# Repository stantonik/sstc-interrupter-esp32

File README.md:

# sstc-interrupter-esp32

**Still in development! Maybe unstable.**

> This project implements a digital interrupter for any Solid State Tesla Coils (SSTC, DRSSTC, ...). The interrupter allows precise control over the arc output using different control modes, making it easy to experiment with pulse timing or MIDI control.

## Features
- **Three Control Modes**
    - Manual: Fully custom PWM output from 0 to 20 kHz, with 1 µs minimum pulse width.
    - USB MIDI: Supports up to 8 simultaneous notes

- **User Interface**
    - SSD1306 64x128 monochrome display
    - Rotary encoder for navigation
    - Two triggers: toggle switch and push button
    - Nice and simple graphical interface

- **Connectivity**
    - USB-C OTG/Serial for MIDI/Programming
    - Toslink SPDIF output

- **Hardware Efficiency**
    - Written entirely in C using ESP-IDF
    - Real-time control via FreeRTOS
    - Optimized for ESP32-S3 hardware
    - Battery powered (200 mAh)

## Demonstration

Playing *Kavinsky - Nighcall*...

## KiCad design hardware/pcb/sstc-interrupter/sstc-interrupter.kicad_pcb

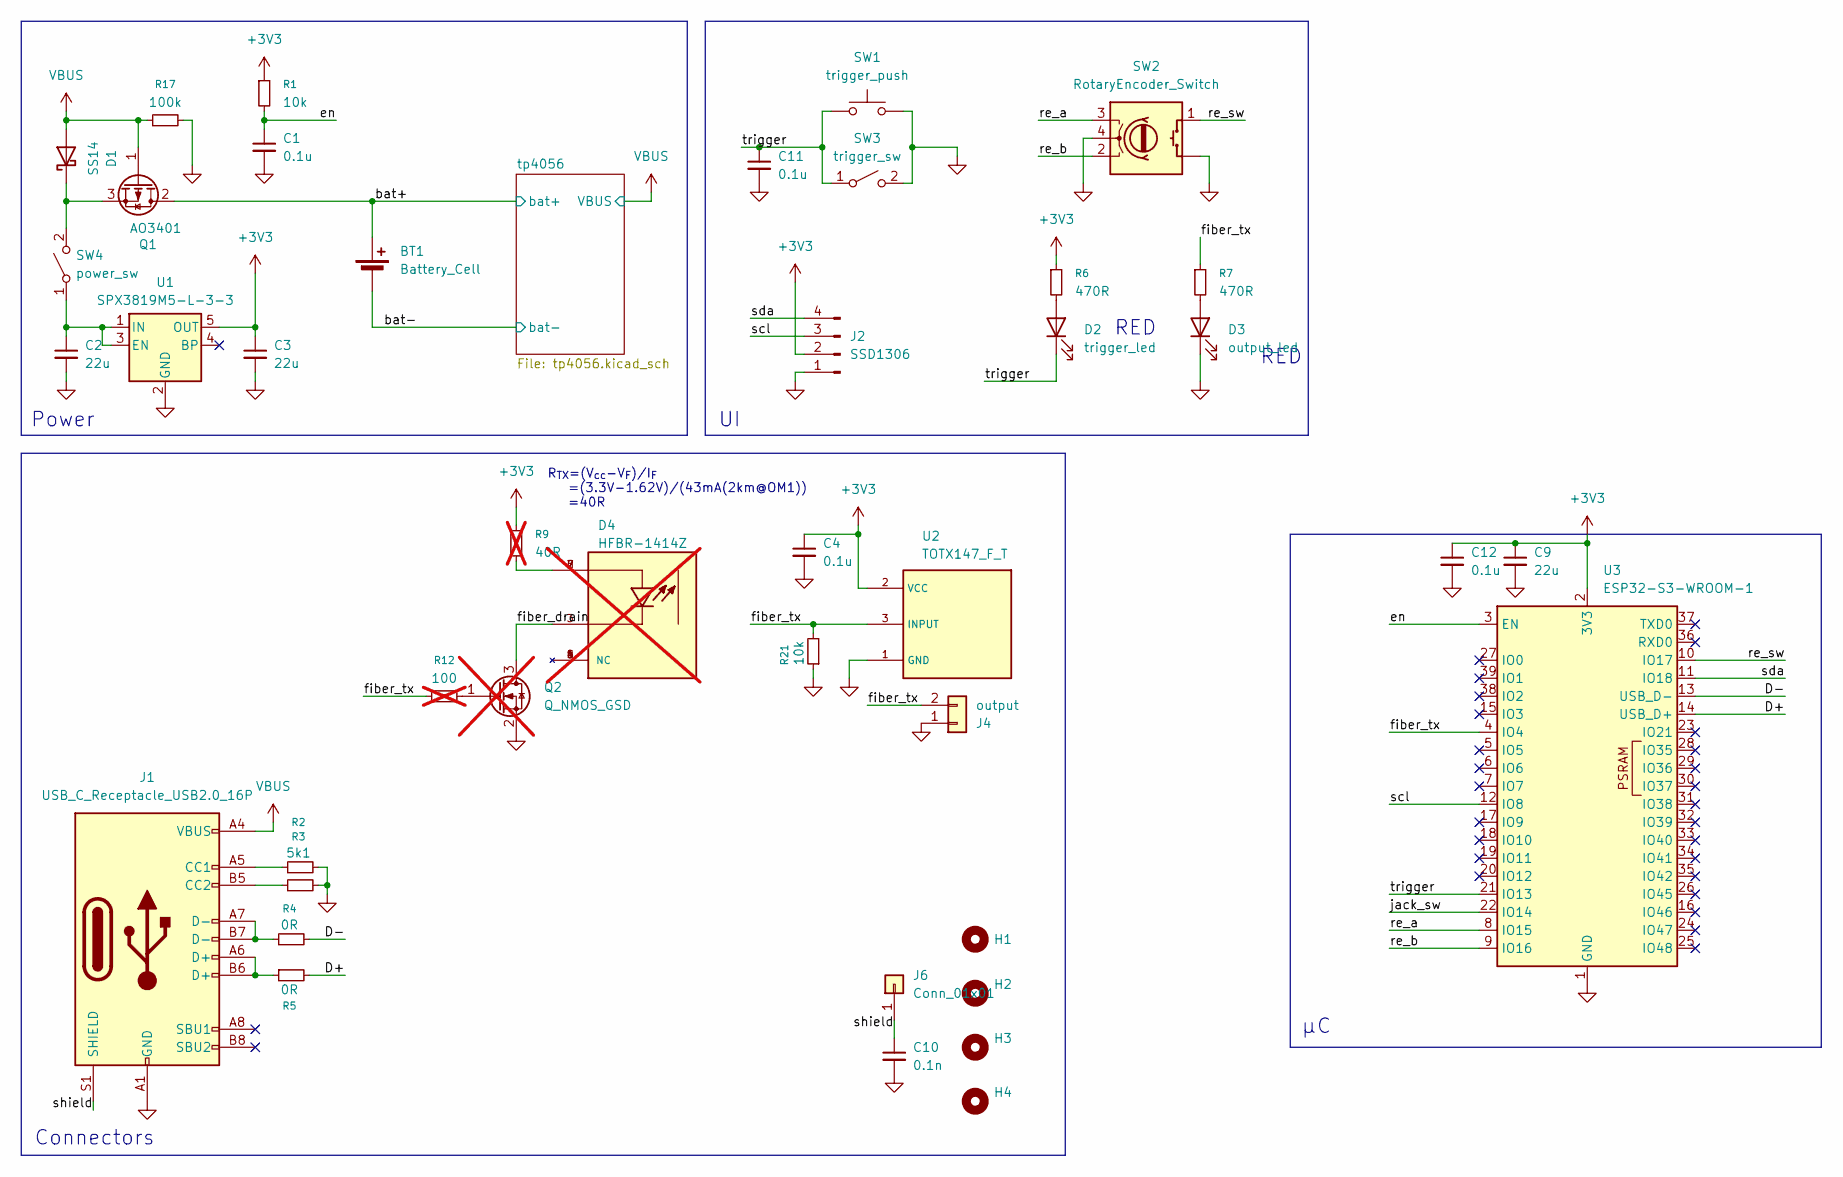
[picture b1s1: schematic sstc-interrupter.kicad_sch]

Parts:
BT1: Battery_Cell; JST_PH_B2B-PH-K_1x02_P2.00mm_Vertical
C1, C4, C11, C12: 0.1u; C_0603_1608Metric_Pad1.08x0.95mm_HandSolder
C2, C3, C9: 22u; C_0805_2012Metric_Pad1.18x1.45mm_HandSolder
C10: 0.1n; C_0805_2012Metric_Pad1.18x1.45mm_HandSolder
D1: SS14; D_SMA
D2: trigger_led; JST_PH_B2B-PH-K_1x02_P2.00mm_Vertical
D3: output_led; JST_PH_B2B-PH-K_1x02_P2.00mm_Vertical
D4: HFBR-1414Z; OPTO_HFBR-1414Z; PARTREV February 15, 2019; not fitted
H1, H2, H3, H4: MountingHole; MountingHole_3.2mm_M3_DIN965
J1: USB_C_Receptacle_USB2.0_16P; USB_C_Receptacle_GCT_USB4105-xx-A_16P_TopMnt_Horizontal
J2: SSD1306; JST_PH_B4B-PH-K_1x04_P2.00mm_Vertical
J4: output; PinHeader_1x02_P2.54mm_Horizontal
J6: Conn_01x01; SolderWire-0.15sqmm_1x01_D0.5mm_OD1.5mm
Q1: AO3401; SOT-23_Handsoldering
Q2: Q_NMOS_GSD; SOT-23-3; not fitted
R1, R21: 10k; R_0603_1608Metric_Pad0.98x0.95mm_HandSolder
R2, R3: 5k1; R_0603_1608Metric_Pad0.98x0.95mm_HandSolder
R4, R5: 0R; R_0603_1608Metric_Pad0.98x0.95mm_HandSolder
R6, R7: 470R; R_0603_1608Metric_Pad0.98x0.95mm_HandSolder
R9: 40R; R_0603_1608Metric_Pad0.98x0.95mm_HandSolder; not fitted
R12: 100; R_0603_1608Metric_Pad0.98x0.95mm_HandSolder; not fitted
R17: 100k; R_0603_1608Metric_Pad0.98x0.95mm_HandSolder
SW1: trigger_push; JST_PH_B2B-PH-K_1x02_P2.00mm_Vertical
SW2: RotaryEncoder_Switch; JST_PH_B4B-PH-K_1x04_P2.00mm_Vertical
SW3: trigger_sw; JST_PH_B2B-PH-K_1x02_P2.00mm_Vertical
SW4: power_sw; JST_PH_B2B-PH-K_1x02_P2.00mm_Vertical
U1: SPX3819M5-L-3-3; SOT-23-5
U2: TOTX147_F_T; TOSHIBA_TORX147_F_T_
U3: ESP32-S3-WROOM-1; ESP32-S3-WROOM-1U

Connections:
+3V3: C3.1, C4.1, C9.1, C12.1, J2.2, R1.1, R6.1, R9.1, U1.5 (OUT), U2.2 (VCC), U3.2 (3V3)
/D+: R5.2, U3.14 (USB_D+)
/D-: R4.2, U3.13 (USB_D-)
/bat+: BT1.1 (+), Q1.2 (D); also elsewhere on the board
/bat-: BT1.2 (-); also elsewhere on the board
/en: C1.1, R1.2, U3.3 (EN)
/fiber_tx: J4.2, R7.1, R12.1, R21.2, U2.3 (INPUT), U3.4 (IO4)
/jack_sw: U3.22 (IO14)
/re_a: SW2.3 (A), U3.8 (IO15)
/re_b: SW2.2 (B), U3.9 (IO16)
/re_sw: SW2.1 (S1), U3.10 (IO17)
/scl: J2.3, U3.12 (IO8)
/sda: J2.4, U3.11 (IO18)
/shield: C10.1, J1.S1 (SHIELD), J6.1 (Pin_1_1)
/trigger: C11.1, D2.2 (K), SW1.1, SW3.1 (A), U3.21 (IO13)
GND: C1.2, C2.2, C3.2, C4.2, C9.2, C10.2, C11.2, C12.2, D3.1 (K), J1.A1 (GND), J1.A12 (GND), J1.B1 (GND), J1.B12 (GND), J2.1, J4.1, Q2.2 (S), R2.2, R3.2, R17.2, R21.1, SW1.2, SW2. (S2), SW2.4 (C), SW3.2 (B), U1.2 (GND), U2.1 (GND), U3.1 (GND), U3.40 (GND), U3.41 (GND); also elsewhere on the board
unnamed: D1.1 (K), Q1.3 (S), SW4.2 (B)
unnamed: D2.1 (A), R6.2
unnamed: D3.2 (A), R7.2
unnamed: D4.1 (NC), D4.4 (NC), D4.5 (NC), D4.8 (NC)
unnamed: D4.2, D4.6, D4.7, R9.2
unnamed: D4.3, Q2.3 (D)
unnamed: J1.A5 (CC1), R2.1
unnamed: J1.B5 (CC2), R3.1
unnamed: J1.A6 (D+), J1.B6 (D+), R5.1
unnamed: J1.A7 (D-), J1.B7 (D-), R4.1
unnamed: Q2.1 (G), R12.2
unnamed: C2.1, SW4.1 (A), U1.1 (IN), U1.3 (EN)
VBUS: D1.2 (A), J1.A4 (VBUS), J1.A9 (VBUS), J1.B4 (VBUS), J1.B9 (VBUS), Q1.1 (G), R17.1; also elsewhere on the board

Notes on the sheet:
Connectors
R_{TX}=(V_{cc}-V_{F})/I_{F} =(3.3V-1.62V)/(43mA(2km@OM1)) =40R
RED
Power

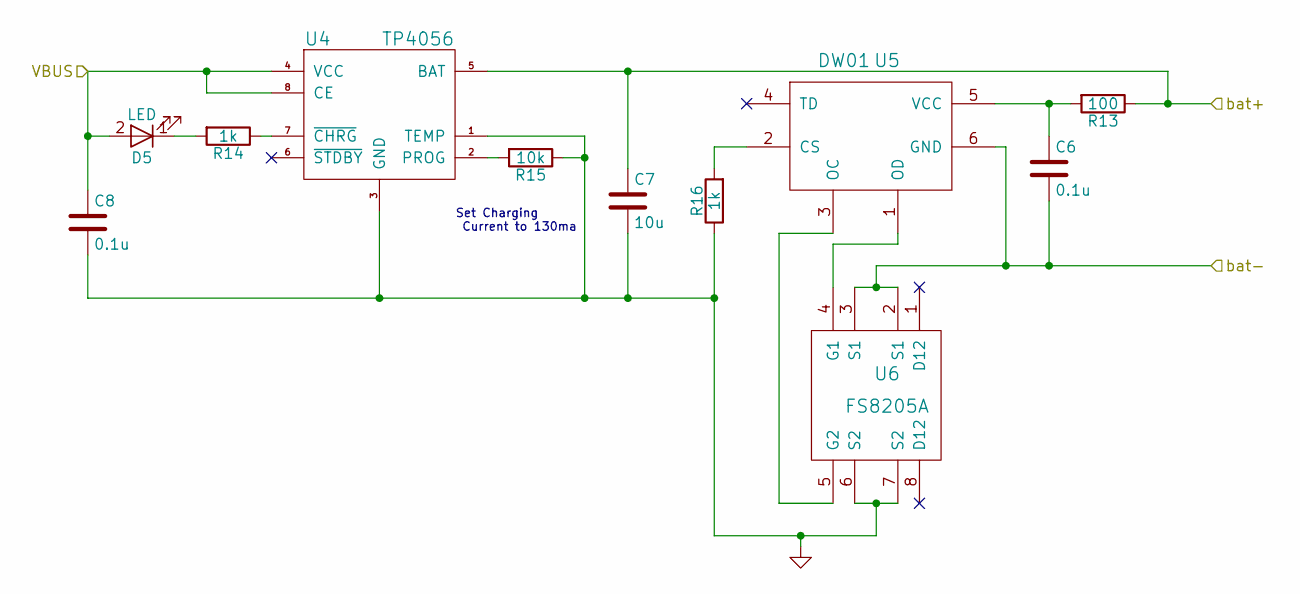
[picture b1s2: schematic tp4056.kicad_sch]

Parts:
C6, C8: 0.1u; C_0603_1608Metric_Pad1.08x0.95mm_HandSolder
C7: 10u; C_0805_2012Metric_Pad1.18x1.45mm_HandSolder
D5: LED; LED_0603_1608Metric_Pad1.05x0.95mm_HandSolder
R13: 100; R_0603_1608Metric_Pad0.98x0.95mm_HandSolder
R14, R16: 1k; R_0603_1608Metric_Pad0.98x0.95mm_HandSolder
R15: 10k; R_0603_1608Metric_Pad0.98x0.95mm_HandSolder
U4: TP4056; SOP-8_3.9x4.9mm_P1.27mm
U5: DW01; SOT-23-6_Handsoldering
U6: FS8205A; TSSOP-8_4.4x3mm_P0.65mm

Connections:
/bat+: C7.1, R13.1, U4.5 (BAT); also elsewhere on the board
/bat-: C6.2, U5.6 (GND), U6.2 (S1), U6.3 (S1); also elsewhere on the board
GND: C7.2, C8.2, R15.1, R16.1, U4.1 (TEMP), U4.3 (GND), U6.6 (S2), U6.7 (S2); also elsewhere on the board
unnamed: D5.1 (K), R14.2
unnamed: R15.2, U4.2 (PROG)
unnamed: R14.1, U4.7 (~CHRG)
unnamed: R16.2, U5.2 (CS)
unnamed: U5.3 (OC), U6.5 (G2)
unnamed: U5.1 (OD), U6.4 (G1)
unnamed: C6.1, R13.2, U5.5 (VCC)
VBUS: C8.1, D5.2 (A), U4.4 (VCC), U4.8 (CE); also elsewhere on the board

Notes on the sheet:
Set Charging Current to 130ma

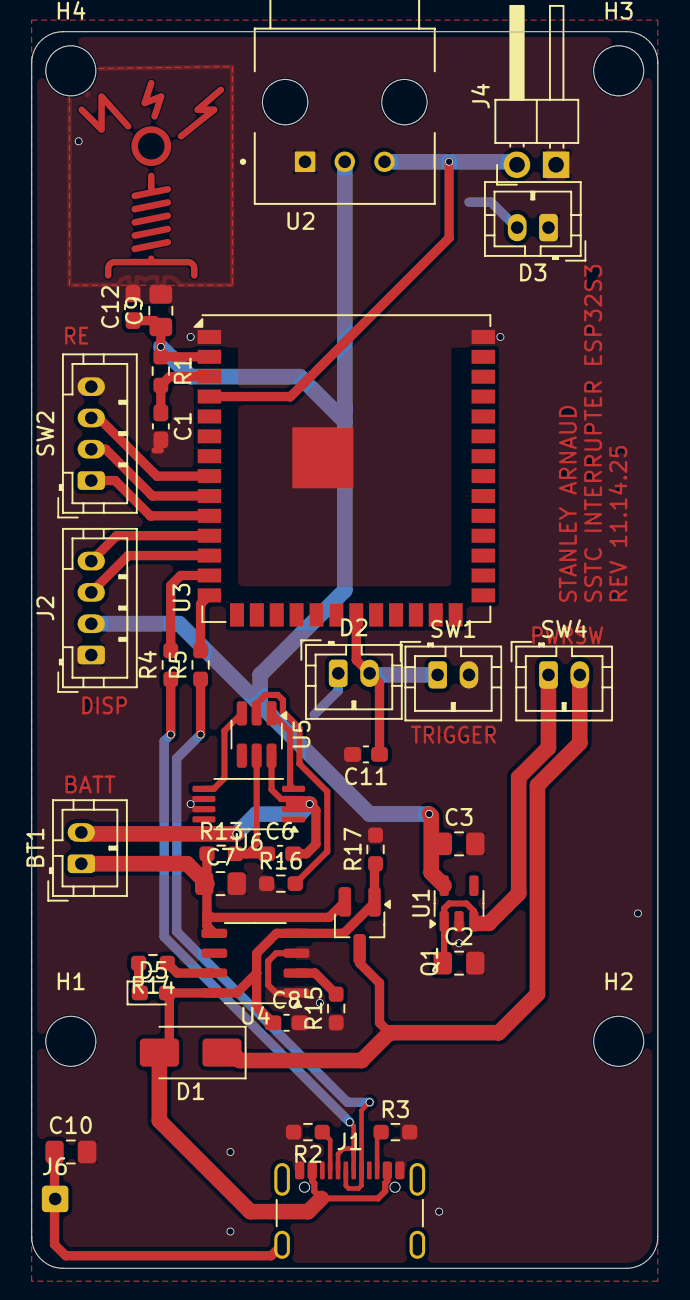
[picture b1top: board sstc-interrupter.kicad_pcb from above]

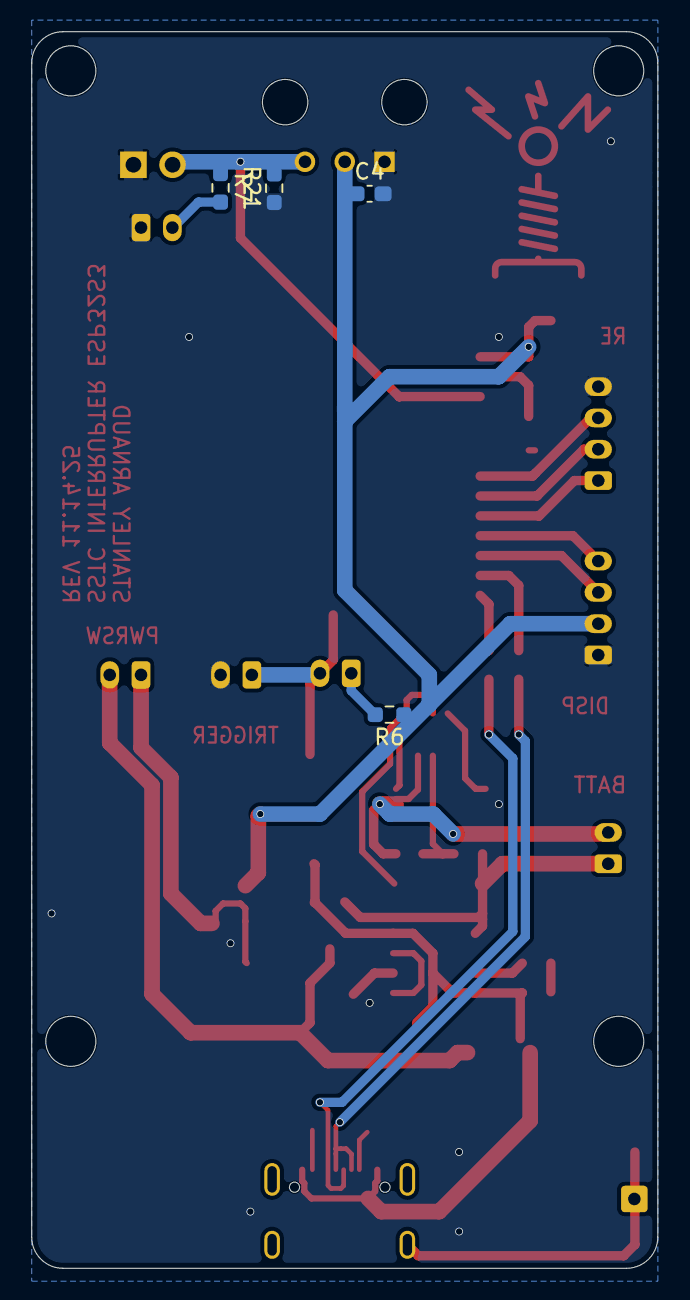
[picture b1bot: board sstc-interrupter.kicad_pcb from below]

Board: 2 copper layers, 40.0 x 79.0 mm, 47 parts (4 on the bottom side), 31 nets.

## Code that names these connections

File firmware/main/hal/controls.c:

/*
 * Copyright (C) 2025 Stanley Arnaud <stantonik@stantonik-mba.local>
 *
 * Distributed under terms of the MIT license.
 */

/**
 * @file controls.c
 * @brief
 *
 * @author Stanley Arnaud
 * @date 10/24/2025
 * @version 0
 */

// -----------------------------------------------------------------------------
// Includes
// -----------------------------------------------------------------------------
#include "controls.h"
#include "esp_log.h"
#include "freertos/FreeRTOS.h"
#include "button_gpio.h"
#include "core/event_bus.h"
#include "encoder.h"
#include "esp_check.h"
#include "iot_button.h"

// -----------------------------------------------------------------------------
// Macros and Constants
// -----------------------------------------------------------------------------
#define TAG "controls"

#define PIN_TRIGGER CONFIG_INTERRUPTER_PIN_TRIGGER

#define PIN_RE_A CONFIG_INTERRUPTER_PIN_RE_A
#define PIN_RE_B CONFIG_INTERRUPTER_PIN_RE_B
#define PIN_RE_SW CONFIG_INTERRUPTER_PIN_RE_SW

// -----------------------------------------------------------------------------
// Static Variables
// -----------------------------------------------------------------------------
static rotary_encoder_t re = {0};
static QueueHandle_t re_queue = NULL;

static button_handle_t trigger_btn = NULL;

static volatile uint8_t state = 0;

// -----------------------------------------------------------------------------
// Static Function Declarations
// -----------------------------------------------------------------------------

// -----------------------------------------------------------------------------
// Static Function Definitions
// -----------------------------------------------------------------------------
static void button_down_cb(void *arg, void *usr_data)
{
    button_handle_t btn = (button_handle_t)arg;
    event_t event = {.source = EVENT_SRC_CONTROLS};

    if (btn == trigger_btn)
    {
        ESP_LOGI(TAG, "Trigger pressed");
        state |= CONTROLS_FLAG_TRIGGER_PRESSED;
        event.type = CONTROLS_EVENT_TRIGGER_PRESSED;
    }

    event_bus_publish(&event);
}

static void button_up_cb(void *arg, void *usr_data)
{
    button_handle_t btn = (button_handle_t)arg;
    event_t event = {.source = EVENT_SRC_CONTROLS};

    if (btn == trigger_btn)
    {
        ESP_LOGI(TAG, "Trigger released");
        state &= ~CONTROLS_FLAG_TRIGGER_PRESSED;
        event.type = CONTROLS_EVENT_TRIGGER_RELEASED;
    }

    event_bus_publish(&event);
}

static void re_task(void *pvParam)
{
    rotary_encoder_event_t re_event;
    event_t event = {.source = EVENT_SRC_CONTROLS};

    while (1)
    {
        xQueueReceive(re_queue, &re_event, portMAX_DELAY);

        switch (re_event.type)
        {
        case RE_ET_BTN_PRESSED:
            event.type = CONTROLS_EVENT_RE_BTN_PRESSED;
            state |= CONTROLS_FLAG_RE_PRESSED;
            break;
        case RE_ET_BTN_RELEASED:
            event.type = CONTROLS_EVENT_RE_BTN_RELEASED;
            state &= ~CONTROLS_FLAG_RE_PRESSED;
            break;
        case RE_ET_BTN_CLICKED:
            event.type = CONTROLS_EVENT_RE_BTN_CLICKED;
            break;
        case RE_ET_BTN_LONG_PRESSED:
            event.type = CONTROLS_EVENT_RE_BTN_LONG_PRESSED;
            break;
        case RE_ET_CHANGED:
            event.type = CONTROLS_EVENT_RE_CHANGED;
            event.value = re_event.diff;
            break;
        default:
            break;
        }

        event_bus_publish(&event);
    }
}

// -----------------------------------------------------------------------------
// Function Definitions
// -----------------------------------------------------------------------------
esp_err_t controls_init(void)
{
    // Rotary encoder
    re_queue = xQueueCreate(4, sizeof(rotary_encoder_event_t));
    ESP_RETURN_ON_ERROR(rotary_encoder_init(re_queue), TAG, "Failed to initialize rotary encoder driver");

    re.pin_a = PIN_RE_A;
    re.pin_b = PIN_RE_B;
    re.pin_btn = PIN_RE_SW;

    ESP_RETURN_ON_ERROR(rotary_encoder_add(&re), TAG, "Failed to create rotary encoder instance");

    ESP_RETURN_ON_FALSE(xTaskCreate(re_task, TAG, configMINIMAL_STACK_SIZE * 8, NULL, 5, NULL) == pdPASS,
        ESP_ERR_NO_MEM, TAG, "Failed to create encoder task");

    // Trigger (switch and push button)
    button_config_t btn_cfg = {0};
    button_gpio_config_t gpio_cfg = {
        .gpio_num = PIN_TRIGGER,
        .active_level = 0,
    };
    ESP_RETURN_ON_ERROR(
        iot_button_new_gpio_device(&btn_cfg, &gpio_cfg, &trigger_btn), TAG, "Failed to create trigger button instance");

    iot_button_register_cb(trigger_btn, BUTTON_PRESS_UP, NULL, button_up_cb, (void *)trigger_btn);
    iot_button_register_cb(trigger_btn, BUTTON_PRESS_DOWN, NULL, button_down_cb, (void *)trigger_btn);

    ESP_LOGI(TAG, "Initializaion succeeded");

    return ESP_OK;
}

uint8_t controls_get_state(void) { return state; }

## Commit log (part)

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2025-11-02 Initial commit
    Proof of concept demonstrating functional hardware and software,
    including three operational modes. Some knob actions and UI features
    are still missing or incomplete.
2025-11-02 fix(gui): correct behavior of power and gdb knob effects
    GDB and PWR knobs now affect the output signal in MIDI mode and LINE-IN mode. But MIDI still needs a GDB knob.
